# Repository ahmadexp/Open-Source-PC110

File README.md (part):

<h1 align="center">Open-Source IBM Palm Top PC110</h1>

<p align="center">
  A complete, open-source reverse engineering of the IBM Palm Top PC110: schematics, PCB layouts,
  ROM and firmware dumps, chip analysis, optical scans, hardware mods, and system tools.
</p>

<p align="center">

</p>

<p align="center">
  <a href="https://github.com/ahmadexp/Open-Source-PC110/wiki"><strong>Wiki / project story</strong></a>
  ·
  <a href="PCB/PC110-Schematics-Combined.pdf"><strong>Combined schematics</strong></a>
  ·
  <a href="Discovery/Service-Manual/"><strong>Service manual</strong></a>
  ·
  <a href="Mods/ROADMAP.md"><strong>Modernization roadmap</strong></a>
  ·
  <a href="Mods/"><strong>Mods</strong></a>
  ·
  <a href="Software/"><strong>Software</strong></a>
</p>

A complete, open-source reverse engineering of the **IBM Palm Top PC110** (type 2431, 1995), a Japanese-market, 486-class subnotebook co-developed by IBM Japan and Ricoh / RIOS Systems. This repository gathers everything needed to understand, repair, recreate, and modernize the machine: recreated schematics and PCB layouts, die-level chip analysis, firmware and BIOS dumps with disassembly, high-resolution optical and X-ray scans, datasheets, and hardware mods.

> **Goal:** preserve the PC110 in full, signal-for-signal, so it can be rebuilt, repaired, emulated, and reimagined long after the last original board has corroded away.

---

## PC110 Atlas platform compatibility

PC110 Atlas brings the PC110 hardware reference and emulator to modern devices.
Quest submission status updated October 13, 2026; other platform statuses last updated October 8, 2026. Features and release availability differ by edition.

### Released editions

| Platform / channel | Compatibility | Download or installation | Availability |
| --- | --- | --- | --- |
| iPhone and iPad | iOS / iPadOS 17 or later | [App Store](https://apps.apple.com/us/app/pc-110/id6801404183) | Available; 1.0.2 (65), released October 7, 2026 |
| iPhone Duo adaptation | Native iOS edition with adaptive inner/outer-display layouts and hinge alignment | [App Store](https://apps.apple.com/us/app/pc-110/id6801404183) | Available in 1.0.2 (65); simulator-tested, with physical-device and guest-runtime validation pending |
| Apple Watch | watchOS 10 or later, paired iPhone | [App Store companion](https://apps.apple.com/us/app/pc-110/id6801404183) | Available; live display, controls, and guest audio from the iPhone session |
| Apple Vision Pro | visionOS 2 or later | [App Store](https://apps.apple.com/us/app/pc-110/id6801404183) | Available; native visionOS edition with local emulation and an interactive 3D PC110 |
| Apple TV | tvOS 17 or later | [App Store](https://apps.apple.com/us/app/pc-110/id6801404183) | Available; hardware, schematics, and history reference with Siri Remote navigation |
| Android phones, tablets, and foldables | Android 8.0 or later; 64-bit ARM64 or x86-64 runtime | [Google Play](https://play.google.com/store/apps/details?id=org.opensourcepc110.atlas) | Available; 1.1.0 (6), published October 8, 2026, with fold-aware layouts, keyboard/mouse support, and optional gamepad controls |
| Wear OS / PC110 Live | Wear OS 3 or later; paired Android phone with matching app and Google Play services | [Google Play companion](https://play.google.com/store/apps/details?id=org.opensourcepc110.atlas) | Available; 1.1.1 (1000007), published October 8, 2026; live display, controls, and optional guest audio |
| Chromebooks and Android gaming handhelds | Compatible Android runtime with Google Play; same Android requirements above | [Google Play](https://play.google.com/store/apps/details?id=org.opensourcepc110.atlas) | Included in Android 1.1.0; resizable workspace and controller support, with physical-device validation still pending |
| Mac App Store edition | macOS 14 or later, Apple M1 or later | [Mac App Store](https://apps.apple.com/us/app/pc-110/id6801404183) | Available |
| Mac desktop / Homebrew | macOS 12 or later; Intel and Apple silicon | [Intel DMG](https://github.com/ahmadexp/homebrew-pc110-atlas/releases/download/desktop-v1.0.0/pc110-atlas-1.0.0-macos-x64.dmg), [Apple silicon DMG](https://github.com/ahmadexp/homebrew-pc110-atlas/releases/download/desktop-v1.0.0/pc110-atlas-1.0.0-macos-arm64.dmg), or [Homebrew instructions](https://github.com/ahmadexp/homebrew-pc110-atlas#install) | Available; Developer ID signed and Apple notarized |
| Windows installers | Windows 10 or later, x64 | [MSI](https://github.com/ahmadexp/homebrew-pc110-atlas/releases/download/desktop-v1.0.0/pc110-atlas-1.0.0-windows-x64.msi) or [EXE](https://github.com/ahmadexp/homebrew-pc110-atlas/releases/download/desktop-v1.0.0/pc110-atlas-1.0.0-windows-x64.exe) | Available |
| Windows / Chocolatey | Windows 10 or later, x64 | [Chocolatey Community package](https://community.chocolatey.org/packages/pc110-atlas/1.0.0) | Approved September 23, 2026; `choco install pc110-atlas` |
| Ubuntu / Snap Store | amd64 and arm64; Linux with snapd | [Snap Store](https://snapcraft.io/pc110-atlas) | Available on stable; `sudo snap install pc110-atlas` |
| Linux / APT | amd64 and arm64; tested on Ubuntu 24.04 | [Signed APT repository and setup](https://ahmadexp.github.io/homebrew-pc110-atlas/) | Available; DEB packages |
| Linux / YUM and DNF | x86_64 and aarch64; compatible RPM distributions | [Signed YUM/DNF repository and setup](https://ahmadexp.github.io/homebrew-pc110-atlas/) | Available; RPM packages |
| Pinokio launcher | Pinokio 8.2+; supported macOS, Windows x64, and Linux x64/ARM64 editions | [Public launcher and installation guide](https://github.com/ahmadexp/pc110-atlas-pinokio) | Available; launches the matching installed edition, not a separate emulator |

### Previews and pending distribution

| Platform / channel | Compatibility | Access or release record | Status |
| --- | --- | --- | --- |
| Meta Quest | Quest 2, Quest Pro, and Quest 3 / 3S; Horizon OS 76 or later; tracked controllers required | [Build 9 corresponding source and release record](https://github.com/ahmadexp/PC110_MiSTer/releases/tag/pc110-quest-1.1.0-9) | Native interactive 3D edition, 1.1.0 (9), submitted to Meta Horizon Store for review on October 13, 2026. Approval pending; not publicly released. Manual release after approval |
| Android XR | Compatible Android XR headset and 64-bit Android runtime | [Google Play Android edition](https://play.google.com/store/apps/details?id=org.opensourcepc110.atlas) | Optional 3D-laptop preview in 1.1.0; simulator-tested, with physical-headset input and performance validation pending |
| Amazon Fire tablets | Compatible Fire OS with Android API 26+ and a 64-bit ARM64 runtime | [Android 1.1.0 source release](https://github.com/ahmadexp/PC110_MiSTer/releases/tag/pc110-android-1.1.0) | Separate Google-services-free build prepared; hardware validation and Amazon Appstore publication pending |
| Raspberry Pi / Pi-Apps | ARM64 desktop; Raspberry Pi OS Bookworm/Trixie or compatible Ubuntu | [1.0.1 review build](https://github.com/ahmadexp/homebrew-pc110-atlas/releases/tag/desktop-v1.0.1) and [testing guide](https://github.com/ahmadexp/homebrew-pc110-atlas/blob/main/desktop/packaging/pi-apps/README.md) | QEMU review build available and tested on Raspberry Pi 5; [Pi-Apps PR #3051](https://github.com/Botspot/pi-apps/pull/3051) remains open |
| Microsoft Store | Windows 10 or later, x64 desktop | Store ID `9P4QHSVPL2VF` | QEMU-enabled 1.0.1.0 submitted September 18; public Store release not confirmed |
| IRIX / Unix X11 | Experimental IRIX 6.5, MIPS n32 target | [Source test kit](https://github.com/ahmadexp/homebrew-pc110-atlas/releases/tag/irix-v1.0.0) and [build instructions](https://github.com/ahmadexp/homebrew-pc110-atlas/blob/main/unix/README.md) | Source only; frontend tested on Linux X11, with SGI hardware testing still required |

### Edition and device notes

- The Meta Quest Early Access candidate includes the detailed 3D laptop, live emulator screen, keyboard and TrackPoint controls, separate Drag/Rotate modes, and optional See-through room view. Quest Pro checks and owner testing are complete only for the documented scenarios; known performance and graphics limitations, remaining manual checks, and untested headset models were disclosed to Meta. Store submission is not approval or a claim that every device has been tested. The linked release provides corresponding source, not a public store installation.
- Apple TV is a reference edition, not a QEMU emulator, and does not import firmware or disk images.
- Apple Watch and Wear OS display a paired phone's running session. QEMU does not run on the watch. Wear OS physical pairing and audio validation remain pending.
- Android requires a 64-bit operating system, not just a 64-bit processor. Android TV / Google TV, cars, 32-bit Android, and Amazon Vega OS are not supported. Physical foldable, Chromebook, handheld/controller, XR, Wear OS, and Fire validation remains incomplete; implementation does not mean every device has been tested.
- The Mac App Store and Homebrew apps are separate editions. Published portable desktop 1.0.0 packages for Intel/Apple silicon Mac, Windows, and Linux use the portable PC110 core, not QEMU, and do not include guest audio. The Raspberry Pi review build and Microsoft Store candidate are separate QEMU-enabled packages.
- Linux packages require compatible system libraries and a graphical desktop. The smaller Unix edition requires a C99 compiler, GNU make, and X11 development libraries.
- Import your own legally obtained compatible system media where supported; guest operating-system compatibility varies by edition.

See [desktop downloads and checksums](https://github.com/ahmadexp/homebrew-pc110-atlas/releases/tag/desktop-v1.0.0),
the [distribution validation record](https://github.com/ahmadexp/homebrew-pc110-atlas/blob/main/desktop/DISTRIBUTION_VALIDATION.md),
and the [Android 1.1.0 corresponding source](https://github.com/ahmadexp/PC110_MiSTer/releases/tag/pc110-android-1.1.0).

## Start here

| If you want to... | Go here |
|---|---|
| Install PC110 Atlas on your device | [Platform compatibility and downloads](#pc110-atlas-platform-compatibility) |
| Understand the full reverse-engineering journey | [Wiki / A Tribute to the IBM PC110](https://github.com/ahmadexp/Open-Source-PC110/wiki) |
| Repair or inspect original hardware | [Unofficial service manual](Discovery/Service-Manual/) and [power sequence guide](Discovery/Power-Sequence/) |
| Review the recreated boards | [PCB projects](PCB/) and [combined schematic PDF](PCB/PC110-Schematics-Combined.pdf) |
| Explore the custom chips and ROMs | [Components](Components/) and [Flash / ROM dumps](Components/Flash/) |
| Work on emulation or system software | [Discovery notes](Discovery/), [PS2 tools](Software/), and [PC110 emulators & FPGA cores](#pc110-emulators--fpga-cores) |
| Build a modernized PC110 variant | [Mods](Mods/) including ITX boards, CPU upgrade work, RAM expansion, and TFT replacement |

## Repository map

| Folder | What you'll find |
|--------|------------------|
| [**Wiki**](https://github.com/ahmadexp/Open-Source-PC110/wiki) | The polished project story and guided tour: why the PC110 matters, how the board was reconstructed, and where to start. |
| [**`PCB/`**](PCB/) | Recreated **KiCad schematics and PCB layouts** for the mainboard, PSU, keyboard membrane, docking station, modem, and 16 MB RAM module. Includes a [combined schematic PDF](PCB/PC110-Schematics-Combined.pdf), fab files, BOMs, and 3D renders. |
| [**`Components/`**](Components/) | **Chip-level reverse engineering**: die-level analysis (with John McMaster), firmware/BIOS/ROM dumps for six chips, disassembly, emulators, and the internal 4 MB disk image. |
| [**`Discovery/`**](Discovery/) | **Deep-dive subsystem notes** for each major chip and bus, plus an unofficial, comprehensive **service & technical reference manual**, a **live hardware dump** from a running unit, and a reverse-engineering of IBM's `PS2.EXE` tool. Start here to understand how it all fits together. |
| [**`Software/`**](Software/) | **Tools for the PC110** — including **PS2TUI**, **PS2GUI**, and **COMrade**, the serial bridge for DOS and Windows 95 control. |
| [**`Mods/`**](Mods/) | **Hardware modifications and redesigns**: ITX-form-factor recreations, a CPU upgrade adapter, a new docking station, a +4 MB RAM mod, a TFT display swap, and Altium ports. |
| [**`Optical/`**](Optical/) | **High-resolution optical scans, X-ray captures, and individual copper-layer images** of every board and the custom chips. |
| [**`Datasheets/`**](Datasheets/) | Datasheets, pinouts, and connector maps for the chips and connectors across the motherboard and peripheral boards. |
| [**`Docs/`**](Docs/) | The project's story — ["A Tribute to the IBM PC110"](Docs/) — covering the sanding, scanning, decapping, and schematic-extraction journey. |

---

## Recreated PCBs ([`PCB/`](PCB/))

All boards are recreated in **KiCad 9.0** (requires the [Alternate KiCad Library](https://alternatekicadlibrary.com/)), with fab files and BOMs.

| Board | Description | Layers |
|-------|-------------|--------|
| Mainboard | Motherboard | 10 |
| PSU | Power supply | 4 |
| Keyboard | Keyboard membrane | 2 + 2 |
| Docking Station | Port expansion | 4 |
| Modem | 14.4 kbps internal modem | 6 |
| RAM-16MB | 16 MB RAM module | 4 |

**[Combined schematic PDF →](PCB/PC110-Schematics-Combined.pdf)**

### Mother Board
- Schematic

- Layout

### Power Supply
- Schematic

- Layout

### Keyboard Membrane
- Schematic

- Layout

### Port Expansion (Docking Station)
- Schematic

- Layout

### 14.4 kbps Internal Modem
- Schematic

- Layout

### 16 MB RAM Module
- Schematic

- Layout

---

## Component Reverse Engineering ([`Components/`](Components/))

### Die-level investigation

A collaboration with [John McMaster](https://siliconpr0n.org/archive/doku.php?id=ibm:pc110) — laser-decapped chips with high-resolution die imaging.

| Designator | Part | Function | Notes |
|------------|------|----------|-------|
| U61 | VL82C420FC5 | "SCAMP IV" chipset (DMA, PIC, PIT, RTC) | [Notes](Components/U61-VL82C420FC5/) |
| U35 | Pluto | Custom I/O gate array | [Notes](Components/U35-Pluto/) |
| U21 | Bowman | Custom system-controller gate array | [Notes](Components/U21-Bowman/) |
| U75 | D17137AGT | TrackPoint controller | [Notes](Components/U75-D17137AGT/) |

### Flash & ROM dumps

Raw readouts plus reverse-engineering analysis (reports, extracted strings, hexdumps, disassembly, and in some cases emulators) for the programmable chips. See [`Components/Flash/`](Components/Flash/).

| Chip | Size | Role |
|------|------|------|
| [Intel E28F002BXT](Components/Flash/E28F002BXT/) | 256 KiB | Main/system **BIOS** (IBM VGA-compatible, APM) — includes BIOS disassembly project |
| [OKI MSM538032E](Components/Flash/OKI-MSM538032E/) | 1 MiB | Japanese/system **font mask ROM** |
| [Eon EN29F040A](Components/Flash/EN29F040A/) | 512 KiB | **Modem/fax board** flash |
| [Mitsubishi M38813E4HP](Components/Flash/M38813E4HP/) | ~16 KiB | **Keyboard controller** firmware (U67) |
| [Mitsubishi M38223E4HP](Components/Flash/M38223E4HP/) | ~16 KiB | **Power-sense** MCU firmware (U6) — includes an emulator |
| [Atmel AT29LV512](Components/Flash/AT29LV512/) | 64 KiB | SanDisk PCMCIA ATA FlashDisk controller (68000) |

### Internal disk image

Images of the PC110's internal 4 MB solid-state drive in [`Components/Internal-Disk-Image/`](Components/Internal-Disk-Image/) (raw `.img` and PowerQuest `.PQI`).

---

## Discovery — subsystem deep-dives ([`Discovery/`](Discovery/))

Reconstructed from schematic recreations, firmware disassembly, die scans, and the datasheets of architectural-twin parts.

| Folder | Subject |
|--------|---------|
| [**Service-Manual**](Discovery/Service-Manual/) | Unofficial comprehensive service & technical reference manual — **start here** |
| [Chipset](Discovery/Chipset/) | VLSI VL82C420 "SCAMP IV" system controller, full pin map |
| [Bowman](Discovery/Bowman/) | U21 main system-controller ASIC |
| [Pluto](Discovery/Pluto/) | U35 I/O gate array (with 6502 disassembler) |
| [65535](Discovery/65535/) | C&T F65535 flat-panel/CRT VGA controller |
| [ES488](Discovery/ES488/) | ESS ES488F "AudioDrive" + YM3812 (OPL2) FM chain |
| [Modem](Discovery/Modem/) | MN195001 single-chip fax engine |
| [PSU-MB-M38](Discovery/PSU-MB-M38/) | U6 M38223E4HP power-sense MCU + connector map |
| [Power-Sequence](Discovery/Power-Sequence/) | Power-on sequence & "won't power on" repair guide |
| [Trackpoint](Discovery/Trackpoint/) | U75 µPD17137A pointing-device controller |
| [Debug](Discovery/Debug/) | 80486SX debug / JTAG headers + a homebrew debug pod |
| [PS2](Discovery/PS2/) | IBM's `PS2.EXE` configuration tool, fully reverse-engineered — including the hidden `_@` commands |
| [Live-Dump](Discovery/Live-Dump/) | Chipset / BIOS / OS state captured from a **running PC110** over a serial link |

---

## Modifications & redesigns ([`Mods/`](Mods/))

| Project | Description |
|---------|-------------|
| [PC110-ITX](Mods/PC110-ITX/) | An ITX-form-factor motherboard reimplementing the PC110, with original BGA parts converted to QFP for easier assembly |
| [PC110-ITX-all-in-one](Mods/PC110-ITX-all-in-one/) | ITX variant that merges the motherboard and docking-station PSU into one board |
| [CPU Upgrade](Mods/CPU%20Upgrade/) | BGA-to-socket adapter work toward a faster CPU (shares the VL82C420 with Taka's 230cs upgrade) |
| [NewDock](Mods/NewDock/) | A redesigned docking station as a standalone KiCad project |
| [RAS4](Mods/RAS4/) | Enables an extra 4 MB of internal RAM by repurposing `VL_D12` as `RAS#4` |
| [TFT](Mods/TFT/) | TFT display replacement, including a BIOS patch image |
| [Altium](Mods/Altium/) | The PCB projects ported from KiCad to Altium |

---

## Optical scans & X-rays ([`Optical/`](Optical/))

High-resolution optical scans, X-ray captures, and individual copper-layer images of every board and the custom chips — including the full 10-layer copper stack of the mainboard, x-rays of the BGA/QFN packages, and corner-stitch die photos for the 486SX, VL82C420, F65535, Bowman, and Pluto. See [`Optical/README.md`](Optical/).

---

## Community

Join the discussion, ask questions, and share your work:

**Discord:** [discord.gg/WvRh6C6WT](https://discord.gg/WvRh6C6WT)
**Facebook group:** [IBM PC110 community](https://www.facebook.com/groups/985746629171739)

---

## How can you help?

- **Review** the schematics and PCB layouts to spot bugs, errors, and issues.
- **Verify** the layout against the schematic and against real hardware.
- **Find** missing datasheets for the custom and undocumented parts.
- **Contribute** firmware / ROM analysis and disassembly.
- **[Fund the next iteration of PCBA](https://gofund.me/716b7dae)** so we can fabricate and test the recreated motherboard.

---

## Press

Featured on **Hackaday**:
- [Reverse Engineering The IBM PC110, One PCB At A Time](https://hackaday.com/2025/04/06/reverse-engineering-the-ibm-pc110-one-pcb-at-a-time/)

Featured on **Taka's blog**:
- [PC110 New PSU](https://garakutaen.sakura.ne.jp/misc2/MlogmP3.html#e0318)
- [PC110 PCB Pattern](https://garakutaen.sakura.ne.jp/misc2/MlogmP1.html#e0130)
- [PC110 PCB Layout creation](https://garakutaen.sakura.ne.jp/misc2/MlogmP2.html#e0208)
- [PC110 New Docking Station PCB](https://garakutaen.sakura.ne.jp/misc2/MlogmP3.html#e0324)
- [X-ray photos of the inside of the PC110's LSI](https://garakutaen.sakura.ne.jp/misc2/MlogmP2.html#e0225)

**Jeff Geerling's YouTube Channel**:
- [Reverse engineering Episode](https://youtu.be/p7IvioiveOo?si=PUlHSzOhwXYEpZJ3&t=217)

**LGR YouTube Channel**:
- [LGR Vlog: VCFMW20](https://www.youtube.com/watch?v=yIwXQicYClw&t=7595s)

**VCFMW20 YouTube Channel**:
- [Archaeology of the IBM PC110](https://www.youtube.com/watch?v=8Uja7g9hQlo)

---

## Acknowledgements

This project would not have been possible without **Kevin Moonlight** (microcontroller ROM extraction), **Mike Lycett** (fundraiser & coordination), **Nick Rogers** (debugging & verification), **John McMaster** (high-resolution die imaging), **CLC / Fred Nielsen** (decapping & silicon prep), and the wider **open hardware & retrocomputing community**.

---

## PC110 Emulators & FPGA cores

**[PC110-EMU](https://github.com/ahmadexp/PC110-EMU)**: an experimental emulator built around the *real* machine artifacts documented here. It boots the actual PC110 BIOS, runs PC DOS and Personaware, and loads the power-sense and keyboard-controller MCU firmware and the Japanese font flash — the very dumps that live in this repository's [`Components/Flash/`](Components/Flash/) folder.

Highlights:

- Boots the real PC110 BIOS and runs **PC DOS** and supported **Personaware** disk images, including the ROM-backed graphical **Easy-Setup** screen.
- Renders the Personaware launcher with **Japanese DBCS glyphs** pulled from the PC110 font flash ([`MSM538032E`](Components/Flash/OKI-MSM538032E/)).
- Loads the **M38223** power-sense MCU and **M38813** MELPS 740 keyboard-controller firmware for diagnostics and controller responses.
- Models the **front LCD status strip** (the startup `IBM` segment display, time, disk, PMCU, KBC, speaker, and setup state).
- Two frontends: a native **macOS SwiftUI** app for bring-up and diagnostics, and a **portable CMake** build (Linux / Windows / macOS) with a headless runner and an optional SDL2 GUI.
- Rich diagnostics: copy-ready CPU state, traces, memory, and text-screen dumps.

> The emulator ships **no copyrighted ROMs** — use the legally obtained dumps from hardware you own. This repo documents where those dumps come from and what each one does.

The macOS frontend running **Personaware**, with live diagnostics and the modeled front LCD:

The ROM-backed graphical **BIOS Easy-Setup** screen:

**[Get the emulator → ahmadexp/PC110-EMU](https://github.com/ahmadexp/PC110-EMU)**

**[PC110-QEMU](https://github.com/ahmadexp/pc110-qemu)**: a QEMU based emulator for the PC110 with support for the BIOS and is able to boot into DOS7 and run Personaware.

It turns out stock QEMU can run the PC110's software once you give it the handful of PC110-specific
hardware bits the software insists on. PC110-QEMU adds three small QEMU device models, all fed by
the *real* ROM dumps archived in this repository:

- **`pc110-fontrom`** — the banked 1 MB **kanji font ROM** (I/O port `0x1160` selects one of 128 ×
  8 KB banks into a window at `0xDE000`, exactly the mechanism DOS/V's `$FONT.SYS` probes), fed by
  the [MSM538032E dump](Components/Flash/OKI-MSM538032E/). This is what makes Personaware's
  Japanese text render.
- **`pc110-chipset`** — a VLSI/SCAMP + power-MCU shim with an optional full-ROM shadow overlay,
  enough to boot the **real PC110 BIOS** ([E28F002BXT dump](Components/Flash/E28F002BXT/)) on QEMU.
- **`pc110-setupcfg`** — a SeaBIOS-safe config-register + power-MCU interface for the Easy-Setup
  program.

With those in place (`-cpu 486 -m 20M -vga cirrus -device pc110-fontrom,romfile=...`):

- **Personaware**, IBM's Japanese pen-centric GUI, boots to its full home screen in ~20 s — every
  applet (Schedule, ToDo, Notebook, Address, EMail, FAX, IR, WorldClock, DrawMemo, …), live clock,
  working mouse, and sharp DBCS kanji rendered from the real font ROM.
- The graphical **BIOS Easy-Setup** runs under SeaBIOS too: the LZW-compressed setup image is
  extracted from the BIOS flash and chain-loaded by a custom floppy boot sector that enters it
  exactly like the real BIOS does — full main menu, config screens, and the bird mascot — and
  exiting Easy-Setup drops you back into Personaware, just like on the real machine.

The repo also ships the supporting tooling: the LZW Easy-Setup extractor, the Easy-Setup boot
loader (with exit/restart routed back to the hard disk), a partition-dump → bootable-disk
converter (the PC110's internal disk images are partition dumps that need an MBR prepended), and
build/run scripts. No ROMs or disk images are included — supply your own legally obtained dumps,
which this repository documents how to make.

**[Get it → ahmadexp/pc110-qemu](https://github.com/ahmadexp/pc110-qemu)**

**[PC110_MiSTer](https://github.com/ahmadexp/PC110_MiSTer)**: the PC110 as an **FPGA core** — not
emulation but a hardware reimplementation, targeting the **MiSTer** platform (**DE10-Nano**) and built
on the `ao486` core infrastructure. Like the emulators above, it is fed by the *real* dumps archived
here.

Verified milestone: **a zero-error POST, IBM Easy-Setup with working keyboard navigation, and an
unattended PC DOS J7.0/V boot into the PersonaWare V1.0 desktop.**

What the core implements, and where it lines up with this repository:

- **486-class CPU** (forced 30 MHz) plus the AT peripheral set — IDE, floppy, VGA, keyboard, mouse.
- **The stock PC110 memory map**: 4 MiB planar RAM + a 16 MiB expansion module — i.e. the factory 20 MB
  configuration documented in [`Discovery/RAM-Module`](Discovery/RAM-Module/readme.md).
- **256 KiB flash mapped at `C0000h–FFFFFh`** — the [E28F002BXT BIOS dump](Components/Flash/E28F002BXT/).
- **Font-ROM banking** with a 1 MiB font image — the [MSM538032E dump](Components/Flash/OKI-MSM538032E/)
  and the `0x1160` bank-select mechanism, which is what makes Japanese text render.
- **PCMCIA and CMOS** interfaces, the **inking** interface
  ([`Discovery/Inking`](Discovery/Inking/)), and PC110-specific board **I/O decode**.

The project is refreshingly candid about its scope — it calls itself *"an engineering core, not yet a
cycle-exact replacement for the whole PC110 planar,"* and documents which parts are **measured** versus
**placeholder** separately. Building needs **Quartus 17.0.2** (provided via a Docker container), with
scripts for ROM preparation, build, and deployment to MiSTer hardware over SSH.

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
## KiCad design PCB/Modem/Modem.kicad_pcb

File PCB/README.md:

## PC110 Recreated PCBs

Here you can find the recreated all the boards [Schematics](https://github.com/ahmadexp/Open-Source-PC110/blob/main/PCB/PC110-Schematics-Combined.pdf).

Mainboard, RAM-16MB, and Keyboard project file require KiCad 9.0 (with the [AKL](https://alternatekicadlibrary.com/) as a requirement).

Other project file require KiCad 10.0.4. footprint and symbol library included each project folder.

Here is a description of each folder:

| Index | Folder         | Description        | Number of Layers | KiCad version |
| ----- | -------------- | ------------------ | ---------------- | ------------- |
| 1     | Mainboard      | Mother Board       | 10               | 9.0           |
| 2     | PSU            | Power Supply       | 4                | 10.0.4        |
| 3     | Keyboard       | Keyboard Membrane  | 2 + 2            | 9.0           |
| 4     | DockingStation | Port Expansion     | 4                | 10.0.4        |
| 5     | Modem          | 14.4 Interal Modem | 6                | 10.0.4        |
| 6     | RAM-16MB       | 16MB RAM Module    | 4                | 9.0           |

Here are some 3D renders of the PCBs

### Mother Board:

- Schematic

- Layout

### Power Supply:

- Schematic

- Layout

### Keyboard Membrane:

- Schematic

- Layout

### Port Expansion (Docking Station):

- Schematic

- Layout

### 14.4 Kbps Internal Modem:

- Schematic

- Layout

### 16MB RAM Module:

- Schematic

- Layout

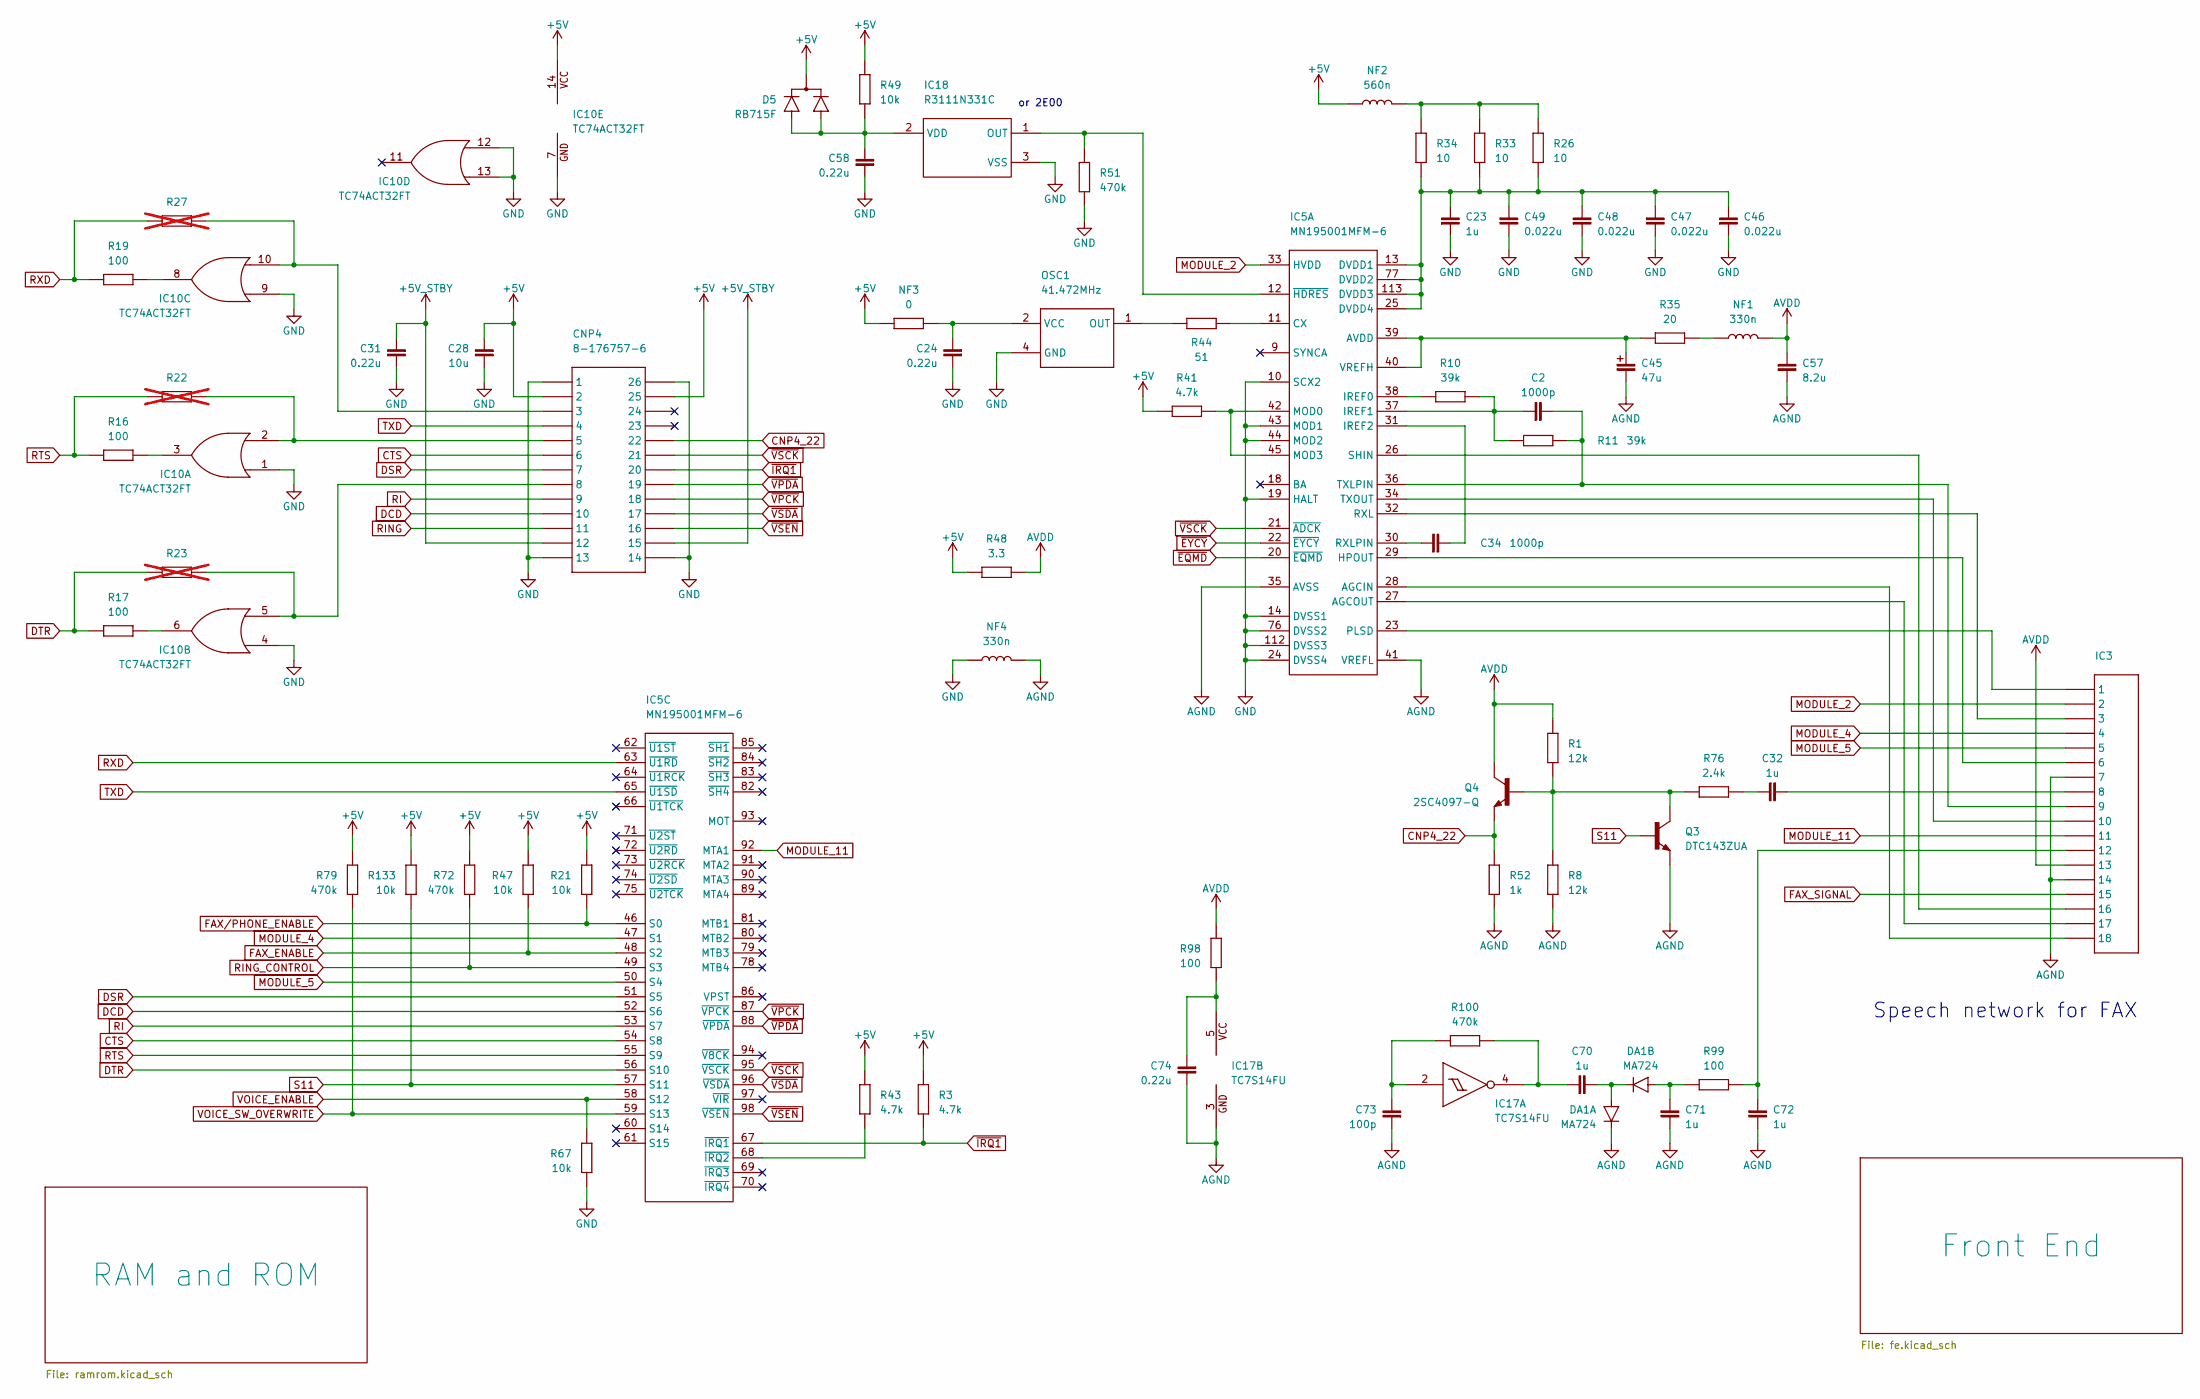
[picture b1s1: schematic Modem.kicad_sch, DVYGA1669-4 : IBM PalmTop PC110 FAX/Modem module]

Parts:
C2, C34: 1000p
C23, C32, C70, C71, C72: 1u
C24, C31, C58, C74: 0.22u
C28: 10u
C45: 47u
C46, C47, C48, C49: 0.022u
C57: 8.2u
C73: 100p
CNP4: 8-176757-6
D5: RB715F
DA1: MA724
IC3: (no value)
IC5: MN195001MFM-6
IC10: TC74ACT32FT
IC17: TC7S14FU
IC18: R3111N331C
NF1, NF4: 330n
NF2: 560n
NF3: 0
OSC1: 41.472MHz
Q3: DTC143ZUA
Q4: 2SC4097-Q
R1, R8: 12k
R3, R41, R43: 4.7k
R10, R11: 39k
R16, R17, R19, R98, R99: 100
R21, R47, R49, R67, R133: 10k
R22, R23, R27: not fitted
R26, R33, R34: 10
R35: 20
R44: 51
R48: 3.3
R51, R72, R79, R100: 470k
R52: 1k
R76: 2.4k

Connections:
+5V: C28.2, CNP4.2, CNP4.25, D5.3 (C), IC10.14 (VCC), NF2.2, NF3.2, R3.2, R21.1, R41.1, R43.1, R47.1, R48.2, R49.1, R72.1, R79.1, R133.1; also elsewhere on the board
+5V_STBY: C31.2, CNP4.12, CNP4.15; also elsewhere on the board
AGND: C45.1 (2), C57.1, C71.2, C72.2, C73.1, C74.2, DA1.3 (C1), IC3.7, IC3.14, IC5.35 (AVSS), IC5.41 (VREFL), IC17.3 (GND), NF4.1, Q3.2 (E), R8.1, R52.1; also elsewhere on the board
AVDD: C57.2, IC3.13, NF1.2, Q4.3 (C), R1.2, R48.1, R98.2
CNP4_22: CNP4.22, Q4.2 (E), R52.2
CTS: CNP4.6, IC5.54 (S8)
DCD: CNP4.10, IC5.52 (S6)
DSR: CNP4.7, IC5.51 (S5)
DTR: IC5.56 (S10), R17.2, R23.1
FAX_ENABLE: IC5.48 (S2), R47.2; also elsewhere on the board
FAX_SIGNAL: IC3.15; also elsewhere on the board
FAX/PHONE_ENABLE: IC5.46 (S0), R21.2; also elsewhere on the board
GND: C23.1, C24.2, C28.1, C31.1, C46.1, C47.2, C48.1, C49.2, C58.2, CNP4.1, CNP4.13, CNP4.14, CNP4.26, IC5.10 (SCX2), IC5.14 (DVSS1), IC5.19 (HALT), IC5.24 (DVSS4), IC5.43 (MOD1), IC5.44 (MOD2), IC5.76 (DVSS2), IC5.112 (DVSS3), IC10.1 (1A), IC10.4 (2A), IC10.7 (GND), IC10.9 (3A), IC10.12 (4A), IC10.13 (4B), IC18.3 (VSS), NF4.2, OSC1.4 (GND), R51.1, R67.1; also elsewhere on the board
MODULE_2: IC3.2, IC5.33 (HVDD)
MODULE_4: IC3.4, IC5.47 (S1)
MODULE_5: IC3.5, IC5.50 (S4)
MODULE_11: IC3.11, IC5.92 (MTA1)
unnamed: C32.1, IC3.8
unnamed: C32.2, R76.1
unnamed: C45.2 (1), IC5.39 (AVDD), IC5.40 (VREFH), R35.2
unnamed: C72.1, IC3.12, R99.2
unnamed: C58.1, D5.1 (A1), D5.2 (A2), IC18.2 (VDD), R49.2
unnamed: C70.2, DA1.1 (A1), DA1.4 (C2)
unnamed: C71.1, DA1.2 (A2), R99.1
unnamed: IC3.18, IC5.28 (AGCIN)
unnamed: IC3.17, IC5.27 (AGCOUT)
unnamed: IC5.11 (CX), R44.1
unnamed: C23.2, C46.2, C47.1, C48.2, C49.1, IC5.13 (DVDD1), IC5.25 (DVDD4), IC5.77 (DVDD2), IC5.113 (DVDD3), R26.1, R33.1, R34.1
unnamed: IC3.6, IC5.29 (HPOUT)
unnamed: IC5.38 (IREF0), R10.1
unnamed: C2.1, IC5.37 (IREF1), R10.2, R11.1
unnamed: C34.2, IC5.31 (IREF2)
unnamed: IC5.42 (MOD0), IC5.45 (MOD3), R41.2
unnamed: IC3.1, IC5.23 (PLSD)
unnamed: IC3.3, IC5.32 (RXL)
unnamed: C34.1, IC5.30 (RXLPIN)
unnamed: IC3.16, IC5.26 (SHIN)
unnamed: C2.2, IC3.9, IC5.36 (TXLPIN), R11.2
unnamed: IC3.10, IC5.34 (TXOUT)
unnamed: IC5.68 (~IRQ2), R43.2
unnamed: CNP4.5, IC10.2 (1B), R22.2
unnamed: IC10.3 (1Y), R16.1
unnamed: CNP4.8, IC10.5 (2B), R23.2
unnamed: IC10.6 (2Y), R17.1
unnamed: CNP4.3, IC10.10 (3B), R27.1
unnamed: IC10.8 (3Y), R19.2
unnamed: C73.2, IC17.2 (I), R100.2
unnamed: C70.1, IC17.4 (O), R100.1
unnamed: C74.1, IC17.5 (VCC), R98.1
unnamed: IC5.12 (~HDRES), IC18.1 (OUT), R51.2
unnamed: NF1.1, R35.1
unnamed: NF2.1, R26.2, R33.2, R34.2
unnamed: OSC1.1 (OUT), R44.2
unnamed: C24.1, NF3.1, OSC1.2 (VCC)
unnamed: Q3.3 (C), Q4.1 (B), R1.1, R8.2, R76.2
RI: CNP4.9, IC5.53 (S7)
RING: CNP4.11; also elsewhere on the board
RING_CONTROL: IC5.49 (S3), R72.2; also elsewhere on the board
RTS: IC5.55 (S9), R16.2, R22.1
RXD: IC5.63 (~U1RD), R19.1, R27.2
S11: IC5.57 (S11), Q3.1 (B), R133.2
TXD: CNP4.4, IC5.65 (~U1SD)
VOICE_ENABLE: IC5.58 (S12), R67.2; also elsewhere on the board
VOICE_SW_OVERWRITE: IC5.59 (S13), R79.2; also elsewhere on the board
~EQMD: IC5.20 (~EQMD)
~EYCY: IC5.22 (~EYCY)
~IRQ1: CNP4.20, IC5.67 (~IRQ1), R3.1
~VPCK: CNP4.18, IC5.87 (~VPCK)
~VPDA: CNP4.19, IC5.88 (~VPDA)
~VSCK: CNP4.21, IC5.21 (~ADCK), IC5.95 (~VSCK)
~VSDA: CNP4.17, IC5.96 (~VSDA)
~VSEN: CNP4.16, IC5.98 (~VSEN)

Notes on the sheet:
Speech network for FAX
or 2E00

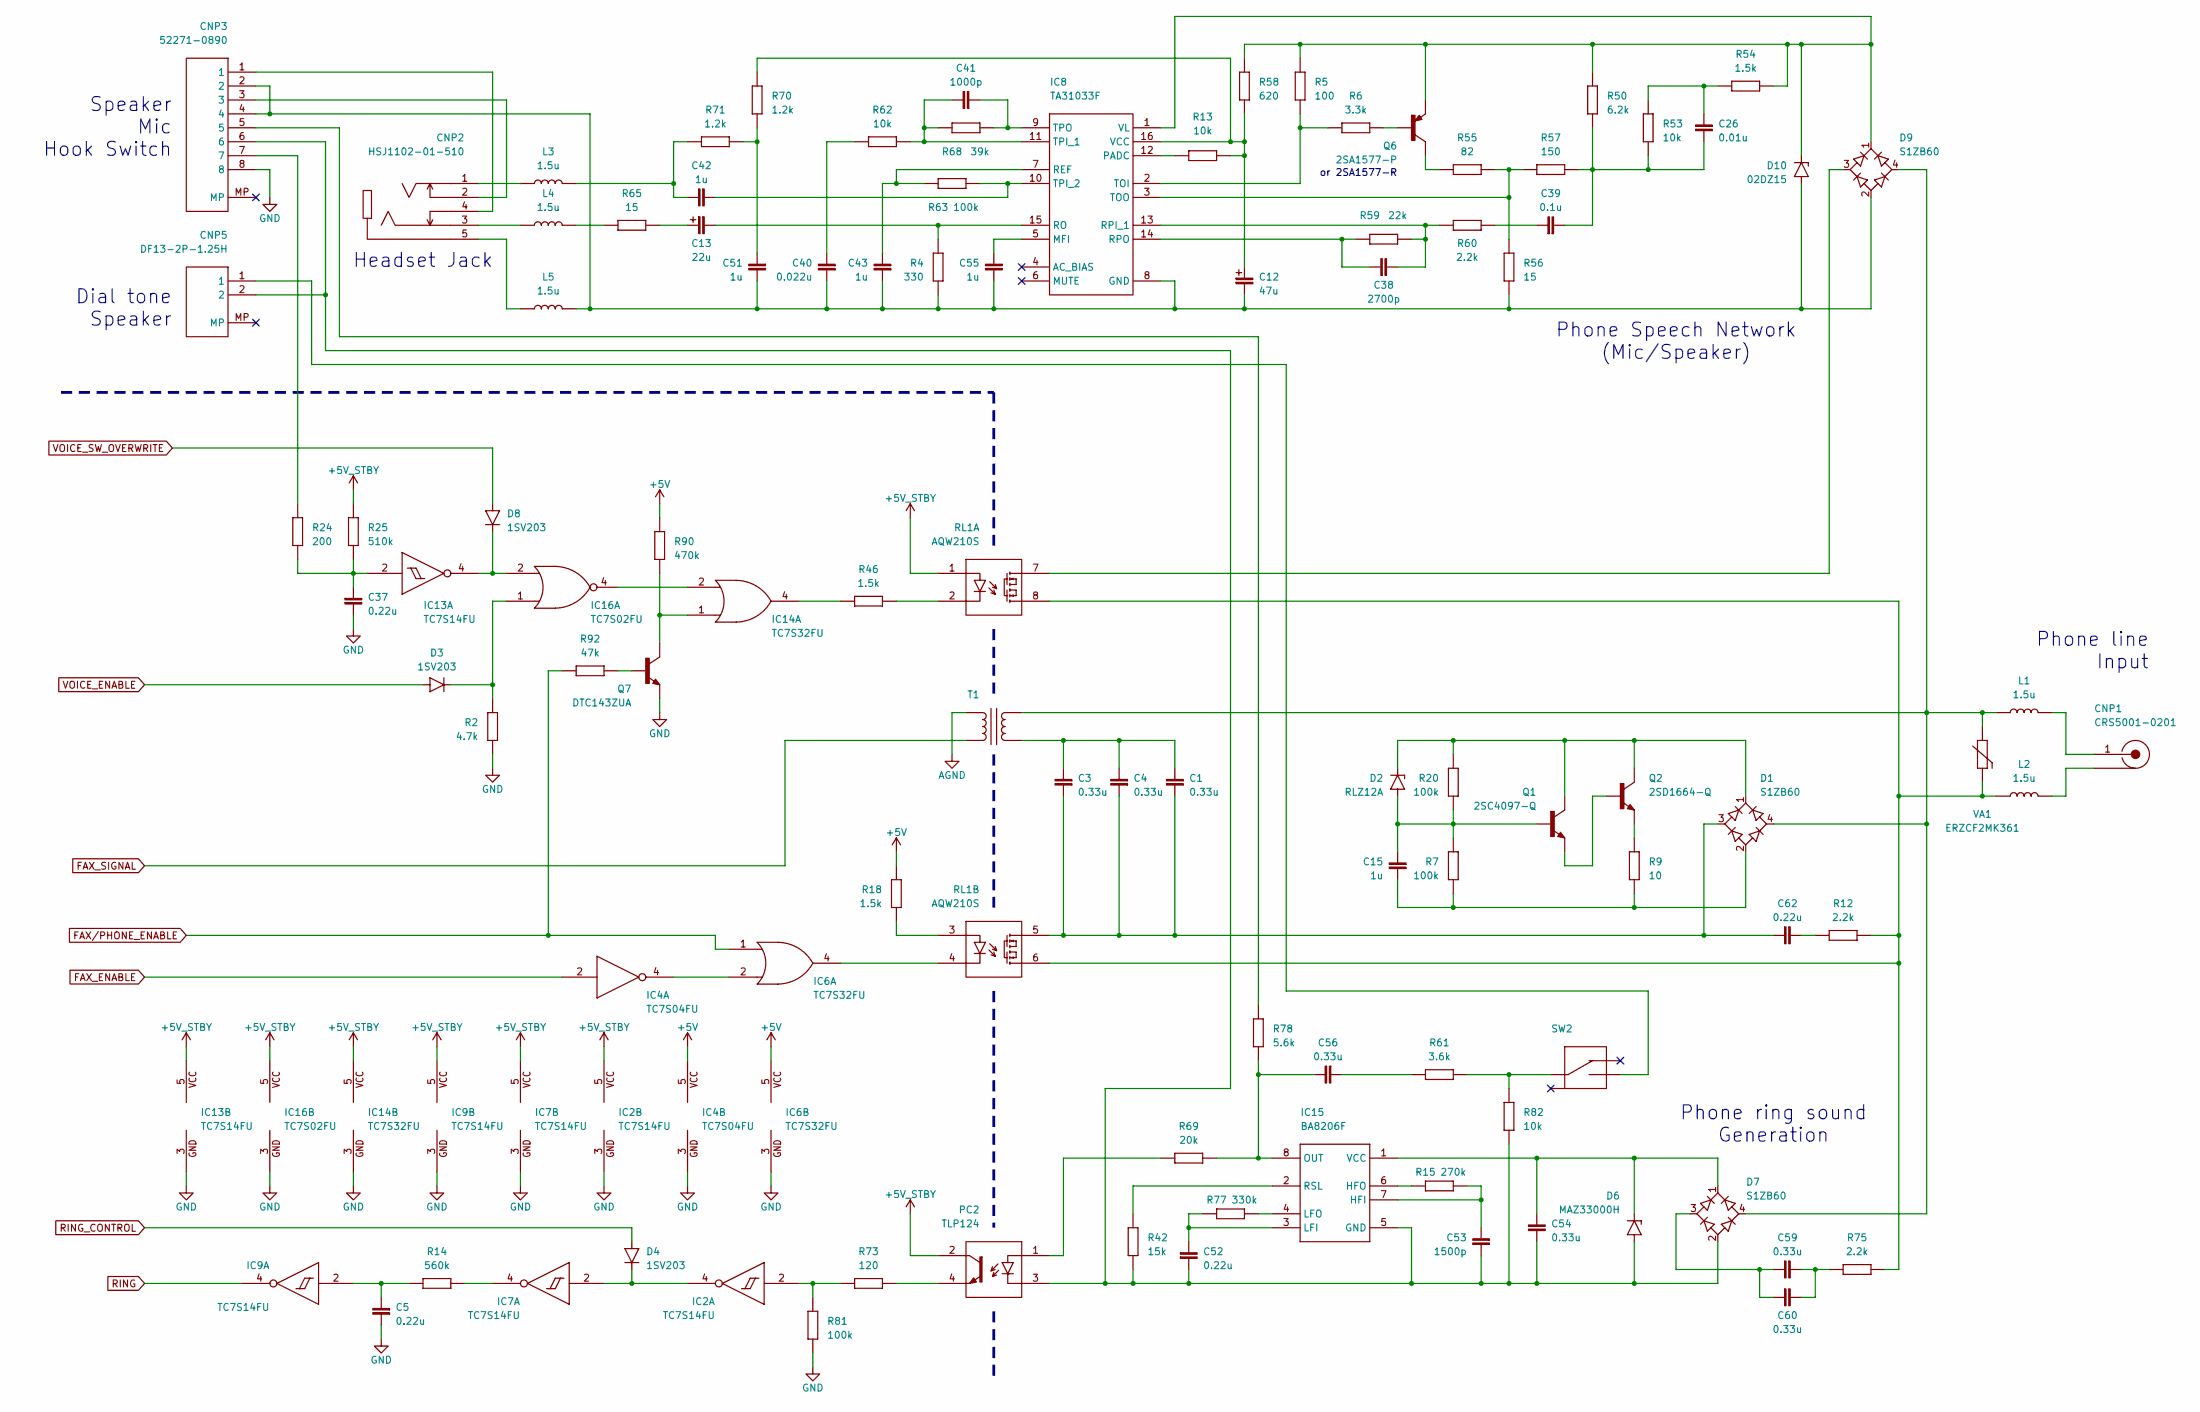
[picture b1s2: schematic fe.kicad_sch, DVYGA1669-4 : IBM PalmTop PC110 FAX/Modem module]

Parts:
C1, C3, C4, C54, C56, C59, C60: 0.33u
C5, C37, C52, C62: 0.22u
C12: 47u
C13: 22u
C15, C42, C43, C51, C55: 1u
C26: 0.01u
C38: 2700p
C39: 0.1u
C40: 0.022u
C41: 1000p
C53: 1500p
CNP1: CRS5001-0201
CNP2: HSJ1102-01-510
CNP3: 52271-0890
CNP5: DF13-2P-1.25H
D1, D7, D9: S1ZB60
D2: RLZ12A
D3, D4, D8: 1SV203
D6: MAZ33000H
D10: 02DZ15
IC2, IC7, IC9, IC13: TC7S14FU
IC4: TC7S04FU
IC6, IC14: TC7S32FU
IC8: TA31033F
IC15: BA8206F
IC16: TC7S02FU
L1, L2, L3, L4, L5: 1.5u
PC2: TLP124
Q1: 2SC4097-Q
Q2: 2SD1664-Q
Q6: 2SA1577-P
Q7: DTC143ZUA
R2: 4.7k
R4: 330
R5: 100
R6: 3.3k
R7, R20, R63, R81: 100k
R9: 10
R12, R60, R75: 2.2k
R13, R53, R62, R82: 10k
R14: 560k
R15: 270k
R18, R46, R54: 1.5k
R24: 200
R25: 510k
R42: 15k
R50: 6.2k
R55: 82
R56, R65: 15
R57: 150
R58: 620
R59: 22k
R61: 3.6k
R68: 39k
R69: 20k
R70, R71: 1.2k
R73: 120
R77: 330k
R78: 5.6k
R90: 470k
R92: 47k
RL1: AQW210S
SW2: (no value)
T1: (no value)
VA1: ERZCF2MK361

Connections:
+5V: IC4.5 (VCC), IC6.5 (VCC), R18.1, R90.1; also elsewhere on the board
+5V_STBY: IC2.5 (VCC), IC7.5 (VCC), IC9.5 (VCC), IC13.5 (VCC), IC14.5 (VCC), IC16.5 (VCC), PC2.2 (C), R25.1, RL1.1; also elsewhere on the board
AGND: T1.2; also elsewhere on the board
FAX_ENABLE: IC4.2 (I); also elsewhere on the board
FAX_SIGNAL: T1.3; also elsewhere on the board
FAX/PHONE_ENABLE: IC6.1 (I0), R92.1; also elsewhere on the board
GND: C5.1, C37.2, CNP3.8, IC2.3 (GND), IC4.3 (GND), IC6.3 (GND), IC7.3 (GND), IC9.3 (GND), IC13.3 (GND), IC14.3 (GND), IC16.3 (GND), Q7.2 (E), R2.1, R81.1; also elsewhere on the board
unnamed: C1.1, C3.1, C4.1, C62.1, D1.3 (AC), RL1.5
unnamed: C1.2, C3.2, C4.2, T1.4
unnamed: C12.2 (1), IC8.16 (VCC), R13.2, R58.1, R70.2
unnamed: C12.1 (2), C40.1, C43.1, C51.2, C55.2, CNP3.2, CNP3.4, D9.2 (-), D10.2 (A), IC8.8 (GND), L5.1, R4.1, R56.2
unnamed: C13.2 (1), R65.2
unnamed: C13.1 (2), IC8.15 (RO), R4.2
unnamed: C26.1, C39.2, R50.2, R53.1, R57.2
unnamed: C26.2, R53.2, R54.2
unnamed: C39.1, R60.2
unnamed: C40.2, R62.2
unnamed: C42.1, L3.1, R71.1
unnamed: C51.1, R70.1, R71.2
unnamed: C56.1, R61.2
unnamed: C59.1, C60.1, D7.3 (AC)
unnamed: C59.2, C60.2, R75.1
unnamed: C62.2, R12.2
unnamed: CNP1.2 (PAD), CNP1.3 (PAD), CNP1.4 (PAD), L2.1
unnamed: CNP1.1, L1.1
unnamed: CNP2.1, L3.2
unnamed: CNP2.2, CNP3.3
unnamed: CNP2.3, L4.2
unnamed: CNP2.4, CNP3.1
unnamed: CNP2.5, L5.2
unnamed: CNP3.5, R78.2
unnamed: CNP3.7, R24.2
unnamed: CNP5.1, SW2.3
unnamed: D1.1 (+), D2.1 (C), Q1.3 (C), Q2.2 (C), R20.1
unnamed: C15.1, D1.2 (-), R7.1, R9.2
unnamed: D1.4 (AC), D7.4 (AC), D9.4 (AC), L1.2, T1.1, VA1.1
unnamed: C15.2, D2.2 (A), Q1.1 (B), R7.2, R20.2
unnamed: D3.1 (C), IC16.1 (I0), R2.2
unnamed: D4.1 (C), IC2.4 (O), IC7.2 (I)
unnamed: C52.2, C53.1, C54.1, CNP3.6, CNP5.2, D6.1 (A), D7.2 (-), IC15.5 (GND), PC2.3 (C), R42.2, R82.1
unnamed: C54.2, D6.3 (C), D7.1 (+), IC15.1 (VCC)
unnamed: D8.1 (C), IC13.4 (O), IC16.2 (I1)
unnamed: D9.3 (AC), RL1.7
unnamed: D9.1 (+), D10.1 (C), IC8.1 (VL), Q6.2 (E), R5.2, R50.1, R54.1, R58.2
unnamed: IC2.2 (I), R73.2, R81.2
unnamed: IC4.4 (O), IC6.2 (I1)
unnamed: IC6.4 (O), RL1.4
unnamed: IC7.4 (O), R14.1
unnamed: C55.1, IC8.5 (MFI)
unnamed: IC8.12 (PADC), R13.1
unnamed: C43.2, IC8.7 (REF), R63.2
unnamed: C38.1, IC8.13 (RPI_1), R59.1, R60.1
unnamed: C38.2, IC8.14 (RPO), R59.2
unnamed: IC8.2 (TOI), R5.1, R6.2
unnamed: IC8.3 (TOO), R55.2, R56.1, R57.1
unnamed: C41.2, IC8.11 (TPI_1), R62.1, R68.2
unnamed: C42.2, IC8.10 (TPI_2), R63.1
unnamed: C41.1, IC8.9 (TPO), R68.1
unnamed: C5.2, IC9.2 (I), R14.2
unnamed: C37.1, IC13.2 (I), R24.1, R25.2
unnamed: IC14.1 (I0), Q7.3 (C), R90.2
unnamed: IC14.2 (I1), IC16.4 (O)
unnamed: IC14.4 (O), R46.1
unnamed: C53.2, IC15.7 (HFI), R15.2
unnamed: IC15.6 (HFO), R15.1
unnamed: C52.1, IC15.3 (LFI), R77.2
unnamed: IC15.4 (LFO), R77.1
unnamed: C56.2, IC15.8 (OUT), R69.1, R78.1
unnamed: IC15.2 (RSL), R42.1
unnamed: L2.2, R12.1, R75.2, RL1.6, RL1.8, VA1.2
unnamed: L4.1, R65.1
unnamed: PC2.1 (A), R69.2
unnamed: PC2.4 (E), R73.1
unnamed: Q1.2 (E), Q2.1 (B)
unnamed: Q2.3 (E), R9.1
unnamed: Q6.1 (B), R6.1
unnamed: Q6.3 (C), R55.1
unnamed: Q7.1 (B), R92.2
unnamed: R18.2, RL1.3
unnamed: R46.2, RL1.2
unnamed: R61.1, R82.2, SW2.2
RING: IC9.4 (O); also elsewhere on the board
RING_CONTROL: D4.2 (A); also elsewhere on the board
VOICE_ENABLE: D3.2 (A); also elsewhere on the board
VOICE_SW_OVERWRITE: D8.2 (A); also elsewhere on the board

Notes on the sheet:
Headset Jack
Phone ring sound Generation
or 2SA1577-R
Phone Speech Network (Mic/Speaker)
Phone line Input
Dial tone Speaker
Speaker Mic Hook Switch

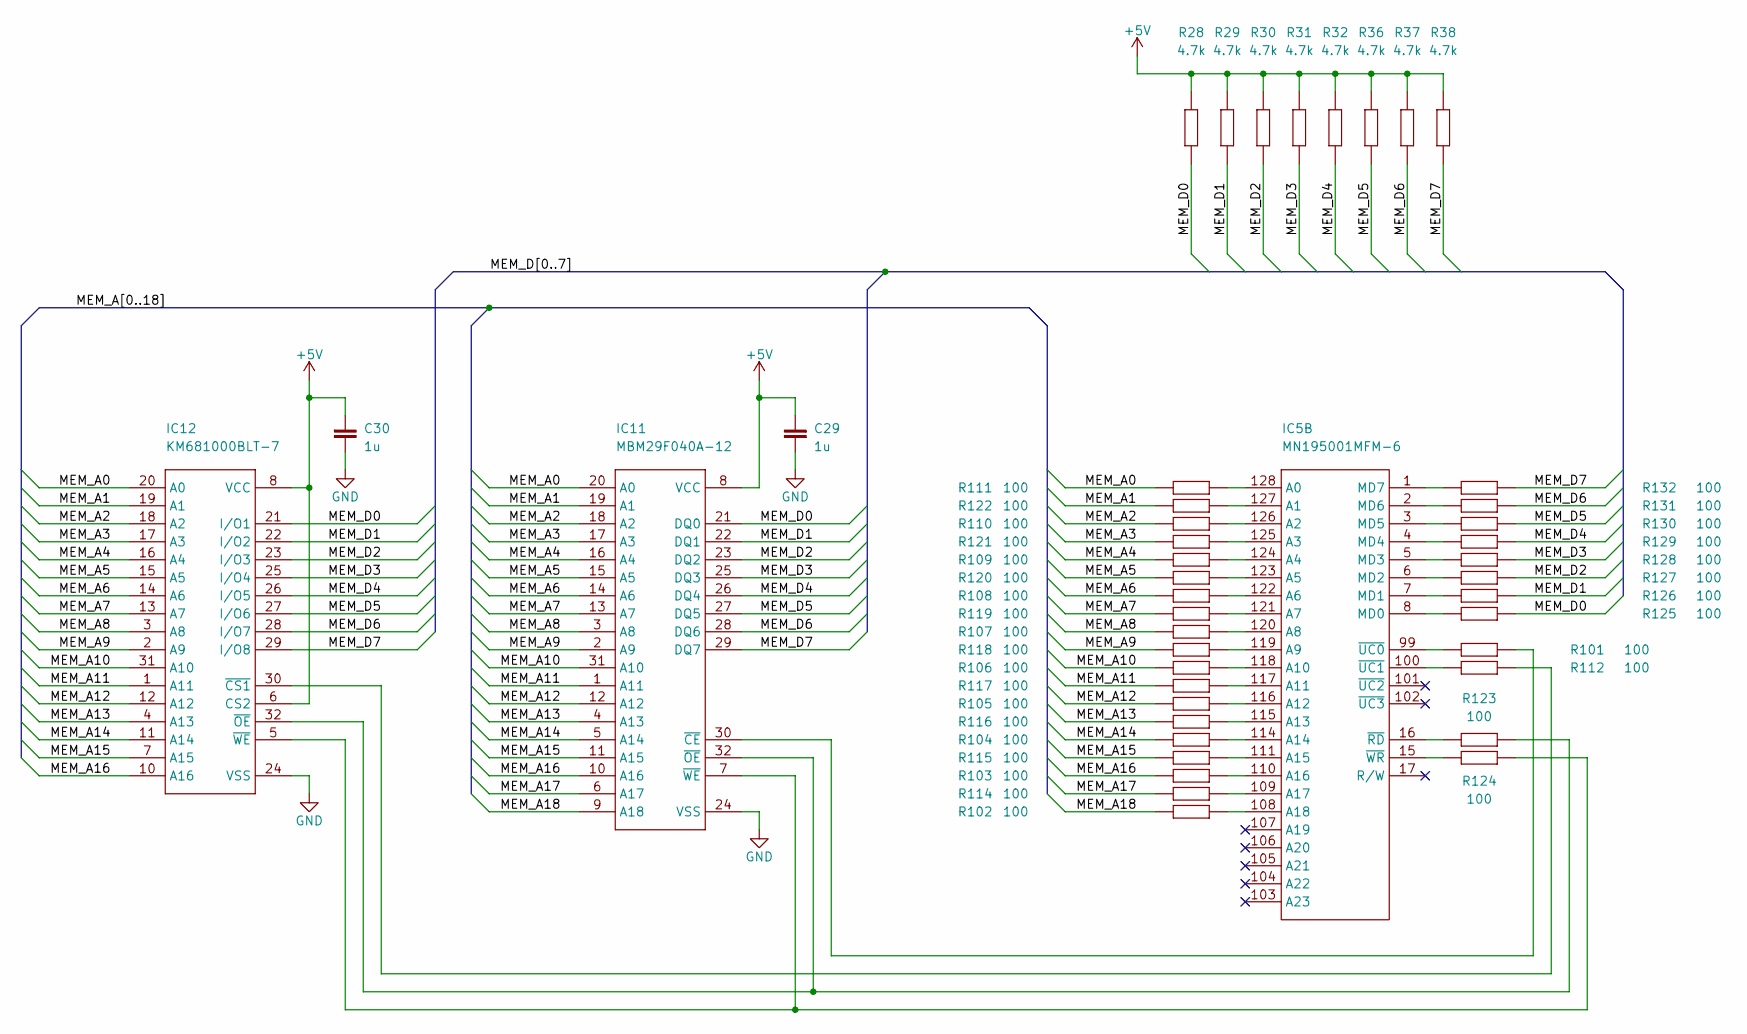
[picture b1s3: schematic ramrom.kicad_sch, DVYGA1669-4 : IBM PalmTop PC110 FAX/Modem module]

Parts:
C29, C30: 1u
IC5: MN195001MFM-6
IC11: MBM29F040A-12
IC12: KM681000BLT-7
R28, R29, R30, R31, R32, R36, R37, R38: 4.7k
R101, R102, R103, R104, R105, R106, R107, R108, R109, R110, R111, R112, R114, R115, R116, R117, R118, R119, R120, R121, R122, R123, R124, R125, R126, R127, R128, R129, R130, R131, R132: 100

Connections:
+5V: C29.2, C30.1, IC11.8 (VCC), IC12.6 (CS2), IC12.8 (VCC), R28.1, R29.1, R30.1, R31.1, R32.1, R36.1, R37.1, R38.1; also elsewhere on the board
/RAM and ROM/MEM_A0: IC11.20 (A0), IC12.20 (A0), R111.1
/RAM and ROM/MEM_A1: IC11.19 (A1), IC12.19 (A1), R122.1
/RAM and ROM/MEM_A2: IC11.18 (A2), IC12.18 (A2), R110.1
/RAM and ROM/MEM_A3: IC11.17 (A3), IC12.17 (A3), R121.1
/RAM and ROM/MEM_A4: IC11.16 (A4), IC12.16 (A4), R109.1
/RAM and ROM/MEM_A5: IC11.15 (A5), IC12.15 (A5), R120.1
/RAM and ROM/MEM_A6: IC11.14 (A6), IC12.14 (A6), R108.1
/RAM and ROM/MEM_A7: IC11.13 (A7), IC12.13 (A7), R119.1
/RAM and ROM/MEM_A8: IC11.3 (A8), IC12.3 (A8), R107.1
/RAM and ROM/MEM_A9: IC11.2 (A9), IC12.2 (A9), R118.1
/RAM and ROM/MEM_A10: IC11.31 (A10), IC12.31 (A10), R106.1
/RAM and ROM/MEM_A11: IC11.1 (A11), IC12.1 (A11), R117.1
/RAM and ROM/MEM_A12: IC11.12 (A12), IC12.12 (A12), R105.1
/RAM and ROM/MEM_A13: IC11.4 (A13), IC12.4 (A13), R116.1
/RAM and ROM/MEM_A14: IC11.5 (A14), IC12.11 (A14), R104.1
/RAM and ROM/MEM_A15: IC11.11 (A15), IC12.7 (A15), R115.1
/RAM and ROM/MEM_A16: IC11.10 (A16), IC12.10 (A16), R103.1
/RAM and ROM/MEM_A17: IC11.6 (A17), R114.1
/RAM and ROM/MEM_A18: IC11.9 (A18), R102.1
/RAM and ROM/MEM_D0: IC11.21 (DQ0), IC12.21 (I/O1), R28.2, R125.1
/RAM and ROM/MEM_D1: IC11.22 (DQ1), IC12.22 (I/O2), R29.2, R126.1
/RAM and ROM/MEM_D2: IC11.23 (DQ2), IC12.23 (I/O3), R30.2, R127.1
/RAM and ROM/MEM_D3: IC11.25 (DQ3), IC12.25 (I/O4), R31.2, R128.1
/RAM and ROM/MEM_D4: IC11.26 (DQ4), IC12.26 (I/O5), R32.2, R129.1
/RAM and ROM/MEM_D5: IC11.27 (DQ5), IC12.27 (I/O6), R36.2, R130.1
/RAM and ROM/MEM_D6: IC11.28 (DQ6), IC12.28 (I/O7), R37.2, R131.1
/RAM and ROM/MEM_D7: IC11.29 (DQ7), IC12.29 (I/O8), R38.2, R132.1
GND: C29.1, C30.2, IC11.24 (VSS), IC12.24 (VSS); also elsewhere on the board
unnamed: IC5.128 (A0), R111.2
unnamed: IC5.127 (A1), R122.2
unnamed: IC5.126 (A2), R110.2
unnamed: IC5.125 (A3), R121.2
unnamed: IC5.124 (A4), R109.2
unnamed: IC5.123 (A5), R120.2
unnamed: IC5.122 (A6), R108.2
unnamed: IC5.121 (A7), R119.2
unnamed: IC5.120 (A8), R107.2
unnamed: IC5.119 (A9), R118.2
unnamed: IC5.118 (A10), R106.2
unnamed: IC5.117 (A11), R117.2
unnamed: IC5.116 (A12), R105.2
unnamed: IC5.115 (A13), R116.2
unnamed: IC5.114 (A14), R104.2
unnamed: IC5.111 (A15), R115.2
unnamed: IC5.110 (A16), R103.2
unnamed: IC5.109 (A17), R114.2
unnamed: IC5.108 (A18), R102.2
unnamed: IC5.8 (MD0), R125.2
unnamed: IC5.7 (MD1), R126.2
unnamed: IC5.6 (MD2), R127.2
unnamed: IC5.5 (MD3), R128.2
unnamed: IC5.4 (MD4), R129.2
unnamed: IC5.3 (MD5), R130.2
unnamed: IC5.2 (MD6), R131.2
unnamed: IC5.1 (MD7), R132.2
unnamed: IC5.16 (~RD), R123.2
unnamed: IC5.99 (~UC0), R101.2
unnamed: IC5.100 (~UC1), R112.2
unnamed: IC5.15 (~WR), R124.2
unnamed: IC11.30 (~CE), R101.1
unnamed: IC11.32 (~OE), IC12.32 (~OE), R123.1
unnamed: IC11.7 (~WE), IC12.5 (~WE), R124.1
unnamed: IC12.30 (~CS1), R112.1

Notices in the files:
README.md:
License:
This project is licensed under the Creative Commons Attribution-NonCommercial 4.0 International License (CC BY-NC 4.0).
You are free to:
- Share, copy and redistribute the material in any medium or format
- Adapt, remix, transform, and build upon the material
Under the following terms:
- Attribution: You must give appropriate credit, provide a link to the license, and indicate if changes were made.
- NonCommercial: You may not use the material for commercial purposes.
For full details, see: https://creativecommons.org/licenses/by-nc/4.0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
